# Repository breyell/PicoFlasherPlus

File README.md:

# PicoFlasher Plus

This project is an addon board to make using [PicoFlasher](https://github.com/X360Tools/PicoFlasher) even easier. Connect wires to the pin header and use the switch to go between flashing 4gb and non-4gb systems. Kits will soon be for sale at [Bonzo's Retro Shop](https://bonzosretro.shop).

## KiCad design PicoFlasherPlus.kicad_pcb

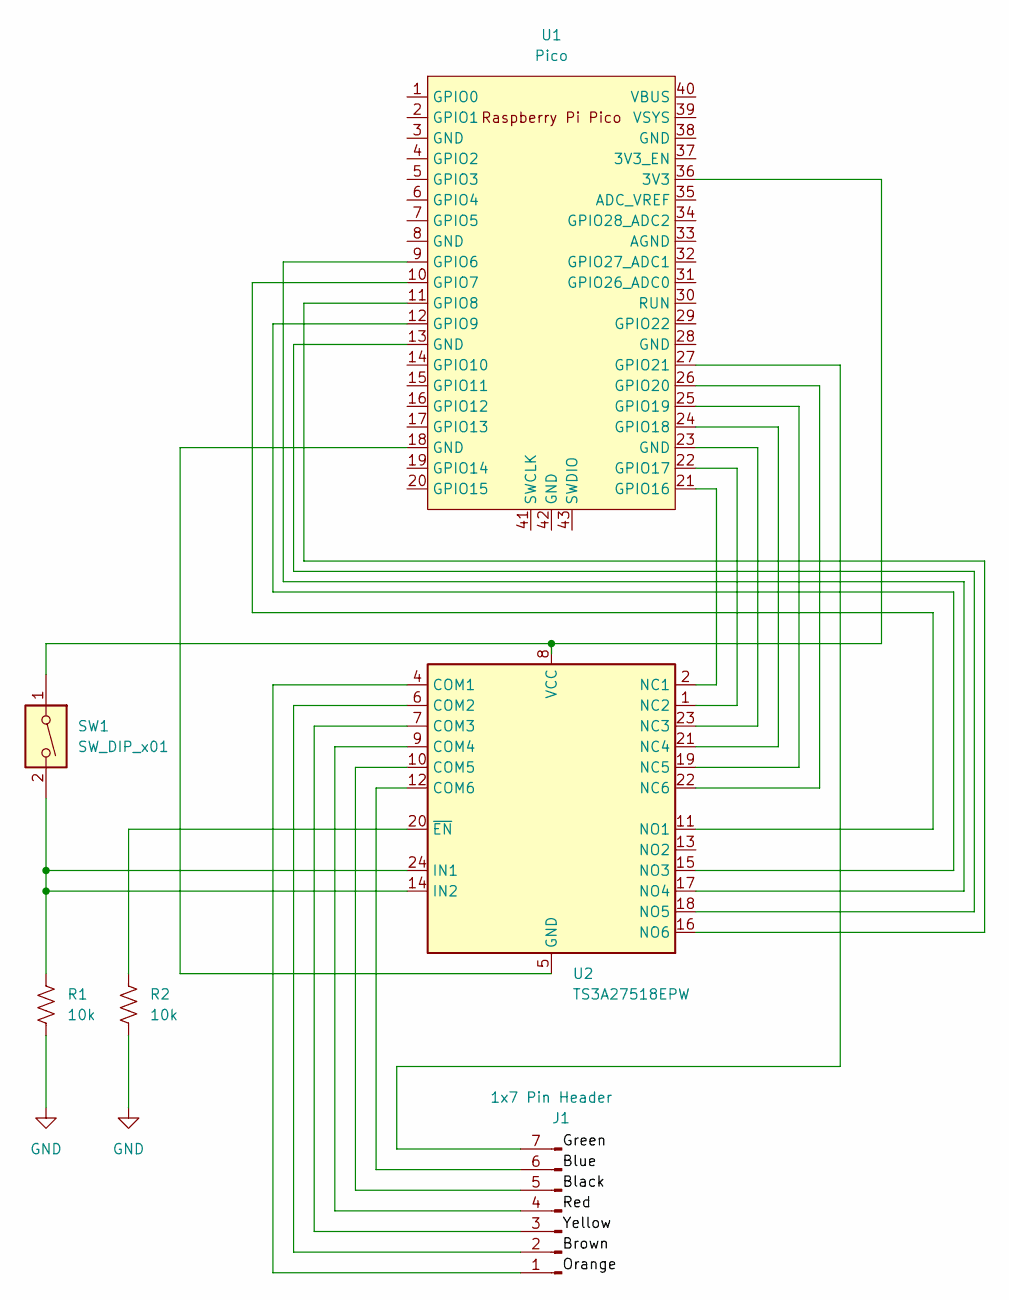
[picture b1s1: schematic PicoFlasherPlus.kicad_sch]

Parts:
J1: 1x7 Pin Header; PinHeader_1x07_P2.54mm_Horizontal
R1, R2: 10k; R_0805_2012Metric_Pad1.20x1.40mm_HandSolder
SW1: SW_DIP_x01; SW_Slide_1P2T_CK_OS102011MS2Q
U1: Pico; RPi_Pico_SMD_TH
U2: TS3A27518EPW; TSSOP-24_4.4x7.8mm_P0.65mm

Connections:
GND: R1.2, R2.2
unnamed: J1.1, U2.4 (COM1)
unnamed: J1.2, U2.6 (COM2)
unnamed: J1.3, U2.7 (COM3)
unnamed: J1.4, U2.9 (COM4)
unnamed: J1.5, U2.10 (COM5)
unnamed: J1.6, U2.12 (COM6)
unnamed: J1.7, U1.27 (GPIO21)
unnamed: R1.1, SW1.2, U2.14 (IN2), U2.24 (IN1)
unnamed: R2.1, U2.20 (~EN)
unnamed: SW1.1, U1.36 (3V3), U2.8 (VCC)
unnamed: U1.9 (GPIO6), U2.17 (NO4)
unnamed: U1.10 (GPIO7), U2.11 (NO1)
unnamed: U1.11 (GPIO8), U2.16 (NO6)
unnamed: U1.12 (GPIO9), U2.15 (NO3)
unnamed: U1.13 (GND), U2.18 (NO5)
unnamed: U1.18 (GND), U2.5 (GND)
unnamed: U1.21 (GPIO16), U2.2 (NC1)
unnamed: U1.22 (GPIO17), U2.1 (NC2)
unnamed: U1.23 (GND), U2.23 (NC3)
unnamed: U1.24 (GPIO18), U2.21 (NC4)
unnamed: U1.25 (GPIO19), U2.19 (NC5)
unnamed: U1.26 (GPIO20), U2.22 (NC6)

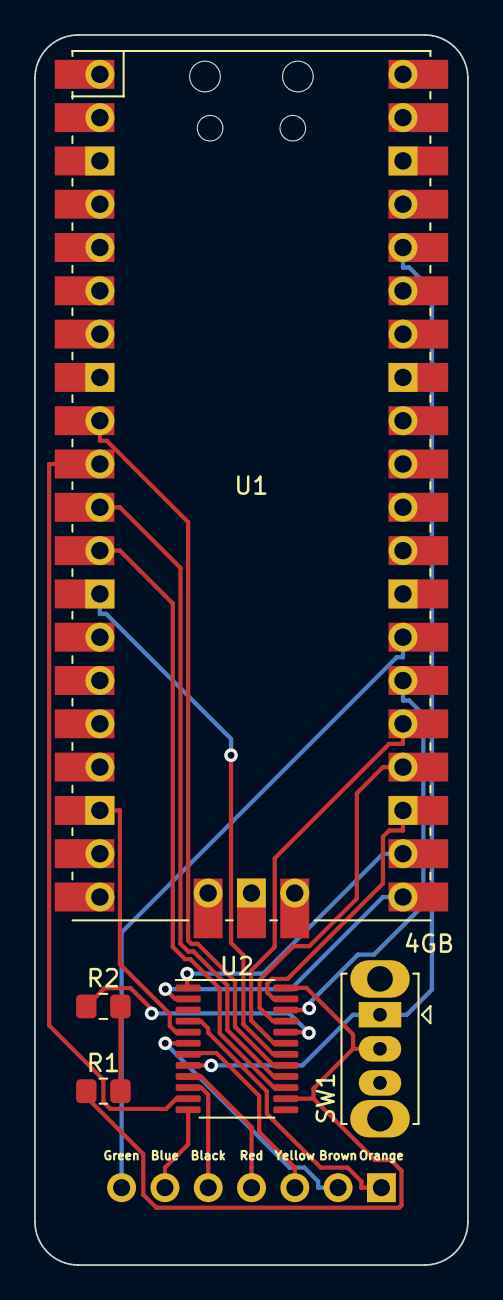
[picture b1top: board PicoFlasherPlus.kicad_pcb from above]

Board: 2 copper layers, 25.4 x 72.2 mm, 6 parts (0 on the bottom side), 23 nets.

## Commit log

2022-12-04 Getting Started
2022-12-05 Round 1
2022-12-31 Add README and image
